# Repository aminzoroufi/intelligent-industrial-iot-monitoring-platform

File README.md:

# Intelligent Industrial IoT Monitoring Platform

> Implementation status: source-complete pre-release demonstrator. Software and
> synthetic evidence are `SIMULATED`; no bench or field verification is claimed.
> Native embedded builds, CAD release checks, post-fix browser evidence, CI on
> GitHub, and publication remain explicit release gates.

A retrofit condition-monitoring demonstrator for a small workshop motor, pump,
or ventilation fan. The system is designed for equipment that is currently
checked manually and where a full SCADA or predictive-maintenance suite would
be disproportionate. It combines temperature, vibration, and DC current
telemetry with offline buffering, Modbus RTU interoperability, deterministic
alarms, and an explainable Isolation Forest comparison.

The reference asset is `motor-01` at site `workshop-demo`. Seeded and simulated
measurements are always labeled as synthetic.

## Architecture

```mermaid
flowchart LR
  S["Sensors and fault fixture"] --> E["ESP32 edge gateway"]
  M["STM32 sensor node"] <-->|"RS-485 / Modbus RTU"| E
  E -->|"Wi-Fi + MQTT"| B["Mosquitto broker"]
  B --> I["Python ingestion service"]
  I --> P[("PostgreSQL")]
  P --> A["FastAPI + anomaly worker"]
  A -->|"REST + authenticated WebSocket"| W["Next.js dashboard"]
```

## Safety boundary

This is a portfolio-grade engineering demonstrator, not a certified safety
controller. Its relay output is limited to a low-voltage demonstration load.
It must not switch mains power or implement an emergency stop, personnel
protection, or unattended safety-critical shutdown. The bench procedure
requires a physical method to remove actuator power.

## Local software demo

Start the local software stack with:

```sh
cp .env.example .env
make demo
make scenario-normal
```

This starts PostgreSQL, Mosquitto, FastAPI, MQTT ingestion, a simulated gateway,
the anomaly worker, and the responsive operator dashboard at
`http://localhost:3000`. The simulated gateway publishes retained health and
safe-state command acknowledgements. ESP32 and STM32 targets, editable Wokwi
projects, Modbus PTY simulation, and the versioned per-device anomaly workflow
are implemented. Python anomaly/Modbus paths pass source and integration tests;
the embedded targets are not compiled in the available environment. The
hardware review package is editable and statically checked but intentionally
un-routed and not released for fabrication because KiCad/FreeCAD execution and
physical evidence are unavailable. Exact evidence and known limits are recorded
in the [verification report](docs/verification-report.md).

Run the local software gates with:

```sh
python -m venv .venv
.venv/bin/pip install -r requirements/ci.lock
npm --prefix web ci
make check
```

The full Compose/API smoke is `make compose-smoke` while the stack is running.
GitHub CI additionally starts a clean stack and runs the desktop/mobile
Playwright happy path.

## Engineering reports

- [English engineering report](docs/report/Intelligent_Industrial_IoT_Monitoring_Platform_EN.pdf)
- [گزارش مهندسی فارسی](docs/report/Intelligent_Industrial_IoT_Monitoring_Platform_FA.pdf)

Both PDFs are generated from editable Markdown sources, use an invariant PDF
build, and pass font/text/page rendering checks plus contact-sheet inspection.
The separate hardware connectivity PDF is marked review-only and is not a
KiCad schematic export or fabrication release.

## Repository map

| Path | Responsibility |
| --- | --- |
| `contracts/` | Versioned MQTT schemas, examples, and topic policy |
| `services/` | FastAPI, MQTT ingestion, and anomaly processes |
| `web/` | Responsive Next.js operator dashboard |
| `firmware/` | ESP32 gateway, STM32 node, shared logic, and host tests |
| `simulator/` | Telemetry, Modbus, Wokwi, and named fault scenarios |
| `hardware/` | KiCad, BOM, fabrication, model provenance, and enclosure |
| `docs/` | Architecture, operation, verification, traceability, and reports |

The dashboard workflows and security boundary are documented in
[`docs/dashboard.md`](docs/dashboard.md).

The repository does not currently include a dashboard screenshot. A previous
browser smoke was observed, but the environment did not permit a new capture
after the live-channel fix; substituting a fabricated or stale image would be
misleading. The committed Playwright flow and GitHub Compose job are the release
path for producing that evidence.

## Verification levels

- `SIMULATED`: demonstrated with host software, test fixtures, or Wokwi.
- `BENCH-VERIFIED`: executed on the documented low-voltage physical bench.
- `FIELD-VALIDATED`: evaluated on real equipment under a controlled protocol.

The current software ingestion and authenticated operations slices are
`SIMULATED`. The ESP32 path is implemented but build-blocked, not verified.
Hardware paths remain explicitly unverified unless physical evidence is
supplied.

## Known limitations and roadmap

The immediate priorities are (1) run ESP-IDF and STM32Cube target builds with
size evidence, (2) migrate and route the board in KiCad 10 and pass native
ERC/DRC before regenerating real fabrication outputs, and (3) run the complete
GitHub CI/Compose/browser flow and capture a truthful dashboard image. The
phased plan and exit criteria are in
[roadmap and limitations](docs/roadmap-and-limitations.md).

## Author and license

Copyright (c) 2026 Amin Zoroufi <aminn.zoroufi@gmail.com>

Source is visible for portfolio inspection under the custom
[Portfolio Source-Available License](LICENSE.md). This is not an open-source
license and it is marked for legal review.

Locked runtime dependency attribution is recorded in the
[dependency/license inventory](docs/dependency-license-inventory.csv).

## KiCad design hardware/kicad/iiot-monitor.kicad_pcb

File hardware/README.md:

# Hardware design status

Revision `A0-UNVERIFIED` is an editable engineering review package for the
extra-low-voltage demonstrator. It is not fabrication-ready. Do not order a PCB,
assemble it, or connect a load from these files until the review gates in
`fabrication/fabrication-status.json` are completed and independently checked.

The canonical, machine-readable source is `design.json`. It records the board
envelope, selected manufacturer part numbers, ratings, placement, pin/net
intent, safety policy, and which 3D shapes are dimensional engineering envelopes
rather than official component models. Run:

```sh
.venv/bin/python scripts/generate_hardware_artifacts.py
.venv/bin/python scripts/generate_hardware_artifacts.py --check
```

The generator creates the BOM, placement, editable KiCad review sources,
mechanical envelopes, FreeCAD rebuild macro, preview SVGs, and review-only
fabrication files. The generation check verifies metadata and model checksums;
it does not substitute for electrical or layout verification.

## Circuit intent

- 5 V SELV/PELV input through resettable overcurrent, polarity, transient, and
  bulk-decoupling stages;
- AP2112K 3.3 V rail with local bulk and high-frequency decoupling;
- ESP32-WROOM-32E gateway with explicit enable/boot bias and UART header;
- TMP117 temperature, INA219 high-side current, 50 mΩ/1 W shunt, and ADXL345
  SPI vibration sensor with interrupt;
- MAX3485 3.3 V half-duplex RS-485, SM712 clamp, selectable 120 Ω termination,
  optional 680 Ω bias, ground reference, and bus test points;
- AO3400A low-side 5 V relay-coil driver, gate resistor/pull-down, and SS14
  flyback diode;
- relay COM/NO connector restricted by project policy to 30 VDC and 2 A. It
  must never switch mains, implement an emergency stop, or control a hazardous
  load.

## KiCad boundary

`iiot-monitor.kicad_pcb` is an editable KiCad board review placement. The
schematic is deliberately retained in KiCad legacy v4 form with a project cache
library because `kicad-cli` is unavailable here; KiCad 10 must import and save it
as `.kicad_sch`. The board is un-routed. Custom review footprints and every pin
mapping must be replaced or verified against current official datasheets and
manufacturer land patterns.

The checked-in ERC/DRC reports say `NOT RUN` and are not passes. The Gerber-like
review set contains outline/status geometry only; copper production geometry is
intentionally absent. After schematic migration, symbol/footprint review,
routing, and actual zero-unexplained-violation ERC/DRC, regenerate outputs with
KiCad 10.0.4 and replace the reports with raw tool output.

## Mechanical and provenance boundary

The project-authored ESP32 and relay STEP files are only datasheet-sized
engineering envelopes. They are visibly named `-envelope`, recorded with source
URL and checksum in `model-provenance.csv`, and must not be described as vendor
3D models. The board assembly STEP is likewise a placement/clearance envelope,
not a KiCad component-accurate export.

`enclosure/iiot-enclosure.FCMacro` is the editable FreeCAD rebuild source.
Project-generated STEP/STL review geometry uses the same board-derived
dimensions. FreeCAD is unavailable in the current environment, so no `.FCStd`
save or FreeCAD-vs-export comparison is claimed.

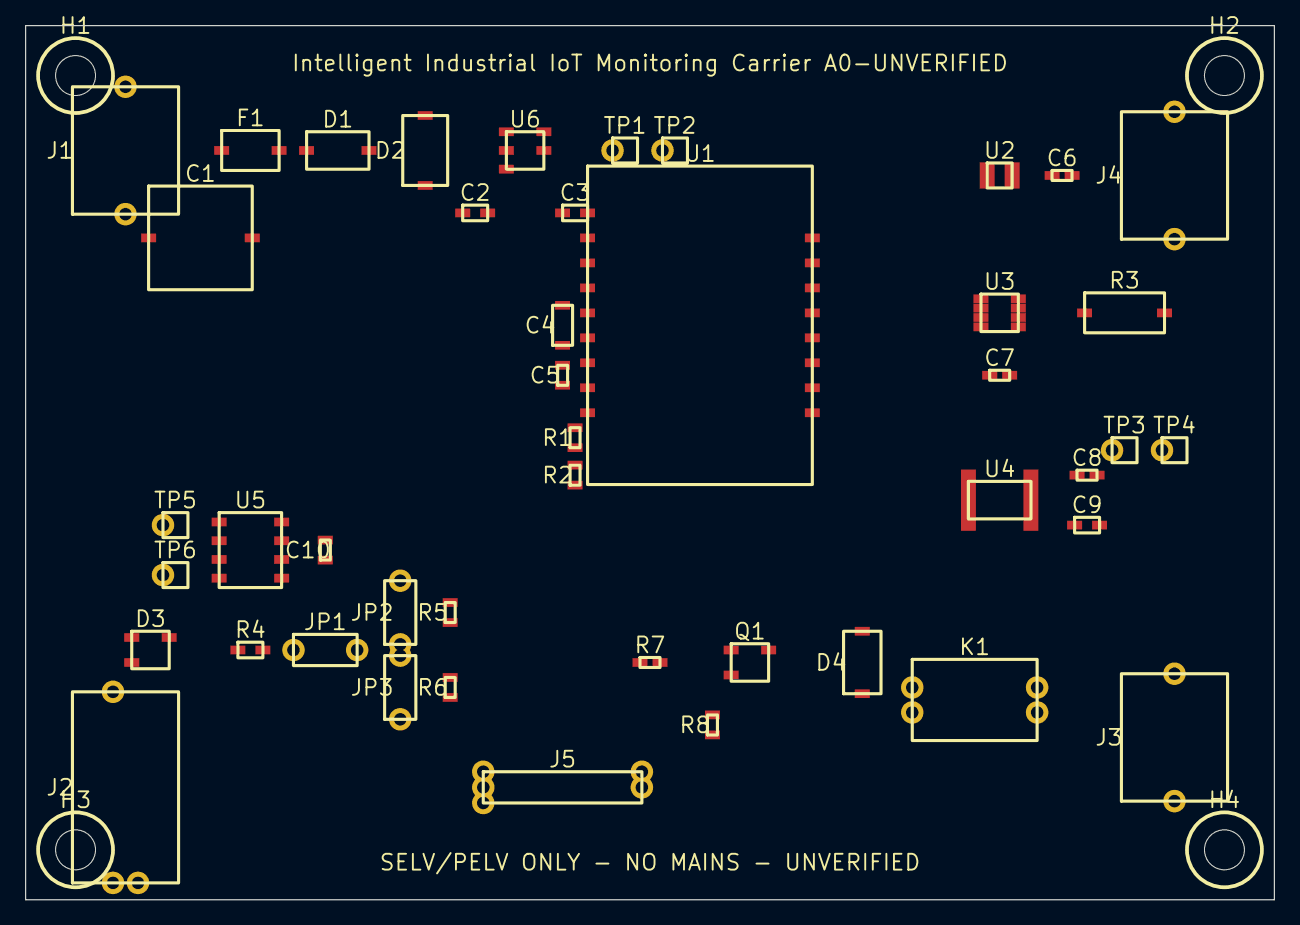
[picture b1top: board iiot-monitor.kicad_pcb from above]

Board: 2 copper layers, 100.0 x 70.0 mm, 49 parts (0 on the bottom side), 27 nets, no tracks yet.

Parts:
C1: 100uF; SMD_D8
C2, C3, C9: 10uF; 0805
C4: 22uF; 1206
C5, C6, C7, C8, C10: 100nF; 0603
D1: SS34; SMA
D2: SMBJ5.0A; SMB
D3: SM712; SOT-23
D4: SS14; SMA
F1: 1.1A PTC; 1812
H1, H2, H3, H4: MountingHole_3.2mm_M3
J1: 5V INPUT; TerminalBlock_2P_5.08mm
J2: MODBUS A/B/GND; TerminalBlock_3P_5.08mm
J3: RELAY COM/NO; TerminalBlock_2P_5.08mm
J4: CURRENT PATH; TerminalBlock_2P_5.08mm
J5: UART PROGRAM; PinHeader_1x05_P2.54mm
JP1: TERM ENABLE; PinHeader_1x02_P2.54mm
JP2: BIAS A; PinHeader_1x02_P2.54mm
JP3: BIAS B; PinHeader_1x02_P2.54mm
K1: G5V-1-DC5; Relay_THT_6.5x10mm
Q1: AO3400A; SOT-23
R1, R2: 10k; 0603
R3: 0.05R 1%; 2512
R4: 120R; 0805
R5, R6: 680R; 0603
R7: 100R; 0603
R8: 100k; 0603
TP1: 3V3; TestPoint_Loop
TP2: GND; TestPoint_Loop
TP3: SDA; TestPoint_Loop
TP4: SCL; TestPoint_Loop
TP5: RS485_A; TestPoint_Loop
TP6: RS485_B; TestPoint_Loop
U1: ESP32-WROOM-32E; Module_ESP32-WROOM-32
U2: TMP117M; WSON-6-2x2mm
U3: INA219A; SOT-23-8
U4: ADXL345; LGA-14-3x5mm
U5: MAX3485; SOIC-8
U6: AP2112K-3.3; SOT-23-5

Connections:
+3V3: C3.1, C4.1, C5.1, C6.1, C7.1, C8.1, C9.1, C10.1, J5.1, JP2.1, R1.1, R2.1, R5.1, TP1.1, U1.2, U2.6, U3.4, U4.1, U4.2, U4.14, U5.8, U6.5
+5V: C1.1, C2.1, D1.2, D2.1, D4.2, J1.1, K1.1, U6.2, U6.3
+5V_FUSED: D1.1, F1.2
ACCEL_CS: U1.29, U4.7
ACCEL_INT: U1.26, U4.8
ESP_BOOT: J5.5, R2.2, U1.25
ESP_EN: R1.2, U1.3
GND: C1.2, C2.2, C3.2, C4.2, C5.2, C6.2, C7.2, C8.2, C9.2, C10.2, D2.2, D3.2, J1.2, J2.3, J5.2, JP3.2, Q1.2, R6.2, R8.2, TP2.1, U1.1, U1.38, U2.2, U3.2, U3.7, U3.8, U4.3, U4.4, U4.5, U4.6, U4.10, U5.5, U6.1
I2C_SCL: TP4.1, U1.36, U2.1, U3.1
I2C_SDA: TP3.1, U1.33, U2.4, U3.3
LOAD_IN: J4.1, R3.1, U3.5
LOAD_OUT: J4.2, R3.2, U3.6
NC: U4.9, U6.4
RELAY_COIL_LOW: D4.1, K1.2, Q1.3
RELAY_COM: J3.1, K1.3
RELAY_CTRL: R7.1, U1.11
RELAY_GATE: Q1.1, R7.2, R8.1
RELAY_NO: J3.2, K1.4
RS485_A: D3.1, J2.1, JP1.1, JP2.2, TP5.1, U5.6
RS485_A_TERM: JP1.2, R4.1
RS485_B: D3.3, J2.2, JP3.1, TP6.1, U5.7
RS485_DE: U1.12, U5.2, U5.3
SPI_MISO: U1.31, U4.12
SPI_MOSI: U1.37, U4.11
SPI_SCK: U1.30, U4.13
UART_RX: J5.4, U1.27, U5.1
UART_TX: J5.3, U1.28, U5.4

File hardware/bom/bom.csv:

references,quantity,manufacturer,manufacturer_part_number,value,package,rating,role,sourcing_note
C1,1,Panasonic,EEE-FK1A101P,100uF,SMD_D8,"100 uF, 10 V",input bulk decoupling,"Verify lifecycle, authorized source, stock, and current datasheet before build"
C10,1,Murata,GRM188R71C104KA01D,100nF,0603,"100 nF, 16 V, X7R",MAX3485 decoupling,"Verify lifecycle, authorized source, stock, and current datasheet before build"
C2,1,Murata,GRM21BR61A106KE19L,10uF,0805,"10 uF, 10 V, X5R",regulator input decoupling,"Verify lifecycle, authorized source, stock, and current datasheet before build"
C3,1,Murata,GRM21BR61A106KE19L,10uF,0805,"10 uF, 10 V, X5R",regulator output decoupling,"Verify lifecycle, authorized source, stock, and current datasheet before build"
C4,1,Murata,GRM31CR61A226ME15L,22uF,1206,"22 uF, 10 V, X5R",ESP32 local bulk decoupling,"Verify lifecycle, authorized source, stock, and current datasheet before build"
C5,1,Murata,GRM188R71C104KA01D,100nF,0603,"100 nF, 16 V, X7R",ESP32 high-frequency decoupling,"Verify lifecycle, authorized source, stock, and current datasheet before build"
C6,1,Murata,GRM188R71C104KA01D,100nF,0603,"100 nF, 16 V, X7R",TMP117 decoupling,"Verify lifecycle, authorized source, stock, and current datasheet before build"
C7,1,Murata,GRM188R71C104KA01D,100nF,0603,"100 nF, 16 V, X7R",INA219 decoupling,"Verify lifecycle, authorized source, stock, and current datasheet before build"
C8,1,Murata,GRM188R71C104KA01D,100nF,0603,"100 nF, 16 V, X7R",ADXL345 high-frequency decoupling,"Verify lifecycle, authorized source, stock, and current datasheet before build"
C9,1,Murata,GRM21BR61A106KE19L,10uF,0805,"10 uF, 10 V, X5R",ADXL345 local bulk decoupling,"Verify lifecycle, authorized source, stock, and current datasheet before build"
D1,1,onsemi,SS34,SS34,SMA,"3 A, 40 V",reverse-polarity series protection,"Verify lifecycle, authorized source, stock, and current datasheet before build"
D2,1,Littelfuse,SMBJ5.0A,SMBJ5.0A,SMB,5 V standoff,5 V transient clamp,"Verify lifecycle, authorized source, stock, and current datasheet before build"
D3,1,Littelfuse,SM712-02HTG,SM712,SOT-23,asymmetric RS-485 TVS,RS-485 transient protection,"Verify lifecycle, authorized source, stock, and current datasheet before build"
D4,1,onsemi,SS14,SS14,SMA,"1 A, 40 V",relay flyback diode,"Verify lifecycle, authorized source, stock, and current datasheet before build"
F1,1,Bourns,MF-MSMF110-2,1.1A PTC,1812,"1.1 A hold, 6 V",resettable input overcurrent protection,"Verify lifecycle, authorized source, stock, and current datasheet before build"
J1,1,Phoenix Contact,1715721,5V INPUT,TerminalBlock_2P_5.08mm,"5 VDC, 1.5 A project limit",SELV/PELV power input,"Verify lifecycle, authorized source, stock, and current datasheet before build"
J2,1,Phoenix Contact,1729128,MODBUS A/B/GND,TerminalBlock_3P_5.08mm,SELV/PELV only,RS-485 field connector,"Verify lifecycle, authorized source, stock, and current datasheet before build"
J3,1,Phoenix Contact,1715721,RELAY COM/NO,TerminalBlock_2P_5.08mm,"30 VDC, 2 A project limit; no mains",extra-low-voltage contact output,"Verify lifecycle, authorized source, stock, and current datasheet before build"
J4,1,Phoenix Contact,1715721,CURRENT PATH,TerminalBlock_2P_5.08mm,0 to 2 A DC project limit,demonstrator current path,"Verify lifecycle, authorized source, stock, and current datasheet before build"
J5,1,Harwin,M20-9990546,UART PROGRAM,PinHeader_1x05_P2.54mm,3.3 V logic,3.3 V UART programming header,"Verify lifecycle, authorized source, stock, and current datasheet before build"
JP1,1,Harwin,M20-9990346,TERM ENABLE,PinHeader_1x02_P2.54mm,3 A,termination enable jumper,"Verify lifecycle, authorized source, stock, and current datasheet before build"
JP2,1,Harwin,M20-9990346,BIAS A,PinHeader_1x02_P2.54mm,3 A,fail-safe A bias enable,"Verify lifecycle, authorized source, stock, and current datasheet before build"
JP3,1,Harwin,M20-9990346,BIAS B,PinHeader_1x02_P2.54mm,3 A,fail-safe B bias enable,"Verify lifecycle, authorized source, stock, and current datasheet before build"
K1,1,Omron Electronics,G5V-1-DC5,G5V-1-DC5,Relay_THT_6.5x10mm,"project-limited to 30 VDC, 2 A",extra-low-voltage demo relay,"Verify lifecycle, authorized source, stock, and current datasheet before build"
Q1,1,Alpha & Omega Semiconductor,AO3400A,AO3400A,SOT-23,"30 V, 5.8 A",low-side relay coil driver,"Verify lifecycle, authorized source, stock, and current datasheet before build"
R1,1,Yageo,RC0603FR-0710KL,10k,0603,0.1 W,ESP32 enable pull-up,"Verify lifecycle, authorized source, stock, and current datasheet before build"
R2,1,Yageo,RC0603FR-0710KL,10k,0603,0.1 W,boot strap pull-up,"Verify lifecycle, authorized source, stock, and current datasheet before build"
R3,1,Vishay,WSL2512R0500FEA,0.05R 1%,2512,"0.05 ohm, 1 W",current shunt,"Verify lifecycle, authorized source, stock, and current datasheet before build"
R4,1,Yageo,RC0805FR-07120RL,120R,0805,0.125 W,selectable RS-485 termination,"Verify lifecycle, authorized source, stock, and current datasheet before build"
R5,1,Yageo,RC0603FR-07680RL,680R,0603,0.1 W,RS-485 A bias resistor,"Verify lifecycle, authorized source, stock, and current datasheet before build"
R6,1,Yageo,RC0603FR-07680RL,680R,0603,0.1 W,RS-485 B bias resistor,"Verify lifecycle, authorized source, stock, and current datasheet before build"
R7,1,Yageo,RC0603FR-07100RL,100R,0603,0.1 W,MOSFET gate resistor,"Verify lifecycle, authorized source, stock, and current datasheet before build"
R8,1,Yageo,RC0603FR-07100KL,100k,0603,0.1 W,MOSFET gate pull-down,"Verify lifecycle, authorized source, stock, and current datasheet before build"
TP1,1,Keystone Electronics,5000,3V3,TestPoint_Loop,3 A,3.3 V test point,"Verify lifecycle, authorized source, stock, and current datasheet before build"
TP2,1,Keystone Electronics,5000,GND,TestPoint_Loop,3 A,ground test point,"Verify lifecycle, authorized source, stock, and current datasheet before build"
TP3,1,Keystone Electronics,5000,SDA,TestPoint_Loop,3 A,I2C data test point,"Verify lifecycle, authorized source, stock, and current datasheet before build"
TP4,1,Keystone Electronics,5000,SCL,TestPoint_Loop,3 A,I2C clock test point,"Verify lifecycle, authorized source, stock, and current datasheet before build"
TP5,1,Keystone Electronics,5000,RS485_A,TestPoint_Loop,3 A,RS-485 A test point,"Verify lifecycle, authorized source, stock, and current datasheet before build"
TP6,1,Keystone Electronics,5000,RS485_B,TestPoint_Loop,3 A,RS-485 B test point,"Verify lifecycle, authorized source, stock, and current datasheet before build"
U1,1,Espressif Systems,ESP32-WROOM-32E-N4,ESP32-WROOM-32E,Module_ESP32-WROOM-32,3.0 to 3.6 V,edge gateway MCU and radio,"Verify lifecycle, authorized source, stock, and current datasheet before build"
U2,1,Texas Instruments,TMP117MAIDRVR,TMP117M,WSON-6-2x2mm,-55 to 150 deg C,digital temperature sensor,"Verify lifecycle, authorized source, stock, and current datasheet before build"
U3,1,Texas Instruments,INA219AIDCNR,INA219A,SOT-23-8,26 V common mode,high-side DC current monitor,"Verify lifecycle, authorized source, stock, and current datasheet before build"
U4,1,Analog Devices,ADXL345BCCZ-RL7,ADXL345,LGA-14-3x5mm,2.0 to 3.6 V,3-axis vibration sensor,"Verify lifecycle, authorized source, stock, and current datasheet before build"
U5,1,Analog Devices,MAX3485ESA+,MAX3485,SOIC-8,3.0 to 3.6 V,3.3 V half-duplex RS-485 transceiver,"Verify lifecycle, authorized source, stock, and current datasheet before build"
U6,1,Diodes Incorporated,AP2112K-3.3TRG1,AP2112K-3.3,SOT-23-5,600 mA,3.3 V logic regulator,"Verify lifecycle, authorized source, stock, and current datasheet before build"

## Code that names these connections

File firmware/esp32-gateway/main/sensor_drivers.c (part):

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#include "freertos/FreeRTOS.h"
#include "freertos/task.h"

#define I2C_SDA_GPIO 21
#define I2C_SCL_GPIO 22
#define TMP117_ADDRESS 0x48
#define INA219_ADDRESS 0x40
#define SPI_MOSI_GPIO 23
#define SPI_MISO_GPIO 19
#define SPI_CLOCK_GPIO 18
#define ADXL345_CS_GPIO 5
#define ADXL345_DRDY_GPIO 34
#define RS485_UART UART_NUM_2
#define RS485_TX_GPIO 17
#define RS485_RX_GPIO 16
#define RS485_DE_GPIO 25

static const char *const TAG = "sensor";
static char modbus_status[16] = "disabled";
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#else
    const i2c_master_bus_config_t bus_config = {
        .i2c_port = I2C_NUM_0,
        .sda_io_num = I2C_SDA_GPIO,
        .scl_io_num = I2C_SCL_GPIO,
        .clk_source = I2C_CLK_SRC_DEFAULT,
        .glitch_ignore_cnt = 7,
        .flags.enable_internal_pullup = true,
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                        "INA219 calibration");

    const spi_bus_config_t spi_bus = {
        .mosi_io_num = SPI_MOSI_GPIO,
        .miso_io_num = SPI_MISO_GPIO,
        .sclk_io_num = SPI_CLOCK_GPIO,
        .quadwp_io_num = -1,
        .quadhd_io_num = -1,
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    ESP_RETURN_ON_ERROR(uart_driver_install(RS485_UART, 256, 0, 0, NULL, 0), TAG,
                        "RS485 UART driver");
    ESP_RETURN_ON_ERROR(uart_param_config(RS485_UART, &uart_config), TAG, "RS485 UART config");
    ESP_RETURN_ON_ERROR(uart_set_pin(RS485_UART, RS485_TX_GPIO, RS485_RX_GPIO, RS485_DE_GPIO,
                                     UART_PIN_NO_CHANGE),
                        TAG, "RS485 pins");
    ESP_RETURN_ON_ERROR(uart_set_mode(RS485_UART, UART_MODE_RS485_HALF_DUPLEX), TAG,
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
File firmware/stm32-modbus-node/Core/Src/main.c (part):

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}

static void transmit_response(const uint8_t *response, size_t length) {
    HAL_GPIO_WritePin(RS485_DE_GPIO_Port, RS485_DE_Pin, GPIO_PIN_SET);
    for (volatile uint32_t delay = 0U; delay < 32U; ++delay) {
        __NOP();
    }
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    }
    while (__HAL_UART_GET_FLAG(&huart2, UART_FLAG_TC) == RESET) {
    }
    HAL_GPIO_WritePin(RS485_DE_GPIO_Port, RS485_DE_Pin, GPIO_PIN_RESET);
}

int main(void) {
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    if (!modbus_node_config_validate(stored)) {
        (void)persist_config(&node.config, NULL);
    }
    HAL_GPIO_WritePin(RS485_DE_GPIO_Port, RS485_DE_Pin, GPIO_PIN_RESET);
    if (HAL_UARTEx_ReceiveToIdle_IT(&huart2, receive_buffer, sizeof(receive_buffer)) != HAL_OK ||
        HAL_TIM_Base_Start_IT(&htim3) != HAL_OK) {
        Error_Handler();
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    __HAL_RCC_GPIOA_CLK_ENABLE();
    __HAL_RCC_GPIOB_CLK_ENABLE();
    __HAL_RCC_GPIOC_CLK_ENABLE();
    HAL_GPIO_WritePin(GPIOB, RS485_DE_Pin, GPIO_PIN_RESET);
    GPIO_InitTypeDef output = {
        .Pin = RS485_DE_Pin,
        .Mode = GPIO_MODE_OUTPUT_PP,
        .Speed = GPIO_SPEED_FREQ_HIGH,
    };
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    HAL_GPIO_Init(GPIOC, &output);
    GPIO_InitTypeDef analog = {.Pin = GPIO_PIN_0, .Mode = GPIO_MODE_ANALOG};
    HAL_GPIO_Init(GPIOA, &analog);
    GPIO_InitTypeDef uart_tx = {
        .Pin = GPIO_PIN_2,
        .Mode = GPIO_MODE_AF_PP,
        .Speed = GPIO_SPEED_FREQ_HIGH,
    };
    HAL_GPIO_Init(GPIOA, &uart_tx);
    GPIO_InitTypeDef uart_rx = {.Pin = GPIO_PIN_3, .Mode = GPIO_MODE_INPUT};
    HAL_GPIO_Init(GPIOA, &uart_rx);
}

static void MX_ADC1_Init(void) {
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

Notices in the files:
firmware/esp32-gateway/main/sensor_drivers.c:
SPDX-FileCopyrightText: 2026 Amin Zoroufi <aminn.zoroufi@gmail.com>
SPDX-License-Identifier: LicenseRef-Portfolio-Source-Available
